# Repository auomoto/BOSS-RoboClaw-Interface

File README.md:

# BOSS-RoboClaw-Interface
 
Interface board that sits on top of the RoboClaw 2x7A controller with a connector for a PI motor.

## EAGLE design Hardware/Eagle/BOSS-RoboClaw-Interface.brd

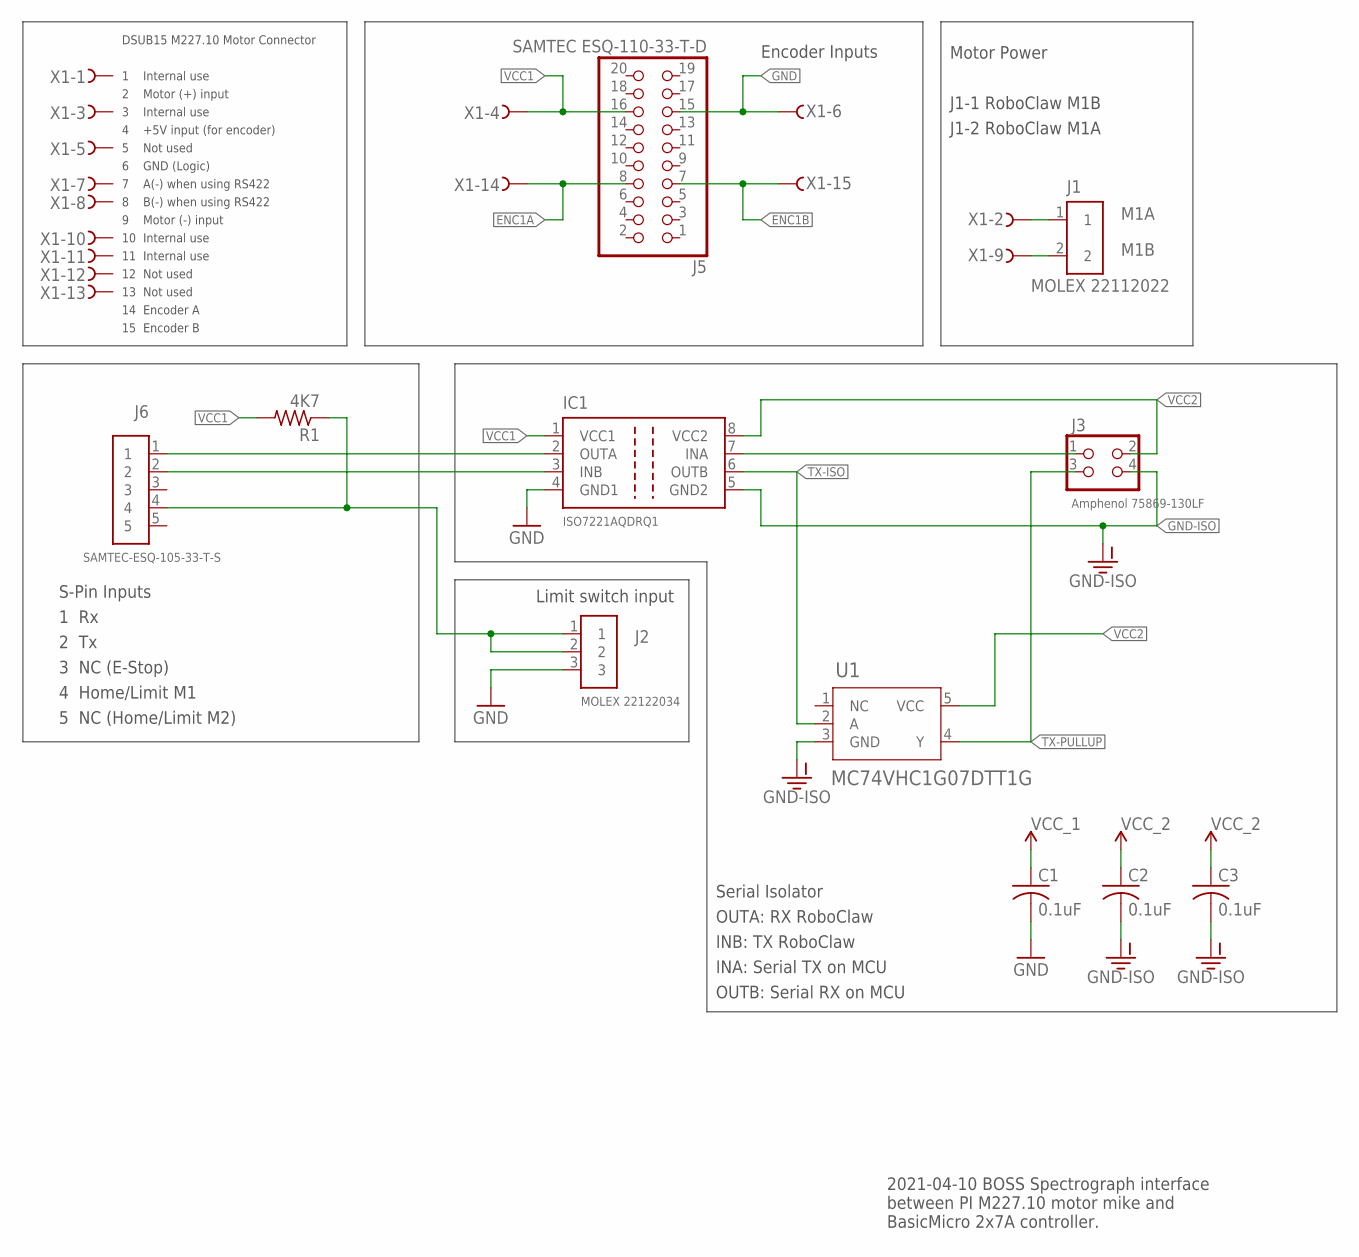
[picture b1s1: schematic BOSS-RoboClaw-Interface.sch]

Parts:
C1, C2, C3: 0.1uF; C0805
IC1: ISO7221AQDRQ1; SO-08-ISO7221
J1: MOLEX 22112022; 1X02-MOLEX-22112022
J2: MOLEX 22122034; 1X03RA-MOLEX-22122034
J3: Amphenol 75869-130LF; 2X02-SHROUD
J5: SAMTEC ESQ-110-33-T-D; 2X10-ESQ-110-33-T-D
J6: SAMTEC-ESQ-105-33-T-S; 1X05-ESQ-105-33-T-S
R1: 4K7; R0805
U1: MC74VHC1G07DTT1G; SOT23-5_ONS-M
X1: Amphenol L77SDAH15SOL2RM8C309; H2R15ST

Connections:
ENC1A: J5.8, X1.14
ENC1B: J5.7, X1.15
GND: C1.2, IC1.4 (GND1), J2.3, J5.15, X1.6
GND-ISO: C2.2, C3.2, IC1.5 (GND2), J3.4, U1.3 (GND)
LIMIT: J2.1, J2.2, J6.4, R1.1
M1A: J1.1, X1.2
M1B: J1.2, X1.9
ROBO-RX: IC1.2 (OUTA), J6.1
ROBO-TX: IC1.3 (INB), J6.2
RX: IC1.7 (INA), J3.1
TX-ISO: IC1.6 (OUTB), U1.2 (A)
TX-PULLUP: J3.3, U1.4 (Y)
VCC1: C1.1, IC1.1 (VCC1), J5.16, R1.2, X1.4
VCC2: C2.1, C3.1, IC1.8 (VCC2), J3.2, U1.5 (VCC)

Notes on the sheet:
DSUB15 M227.10 Motor Connector 1 Internal use 2 Motor (+) input 3 Internal use 4 +5V input (for encoder) 5 Not used 6 GND (Logic) 7 A(-) when using RS422 8 B(-) when using RS422 9 Motor (-) input 10 Internal use 11 Internal use 12 Not used 13 Not used 14 Encoder A 15 Encoder B
Motor Power J1-1 RoboClaw M1B J1-2 RoboClaw M1A
Limit switch input
S-Pin Inputs 1 Rx 2 Tx 3 NC (E-Stop) 4 Home/Limit M1 5 NC (Home/Limit M2)
Serial Isolator OUTA: RX RoboClaw INB: TX RoboClaw INA: Serial TX on MCU OUTB: Serial RX on MCU
Encoder Inputs
2021-04-10 BOSS Spectrograph interface between PI M227.10 motor mike and BasicMicro 2x7A controller.

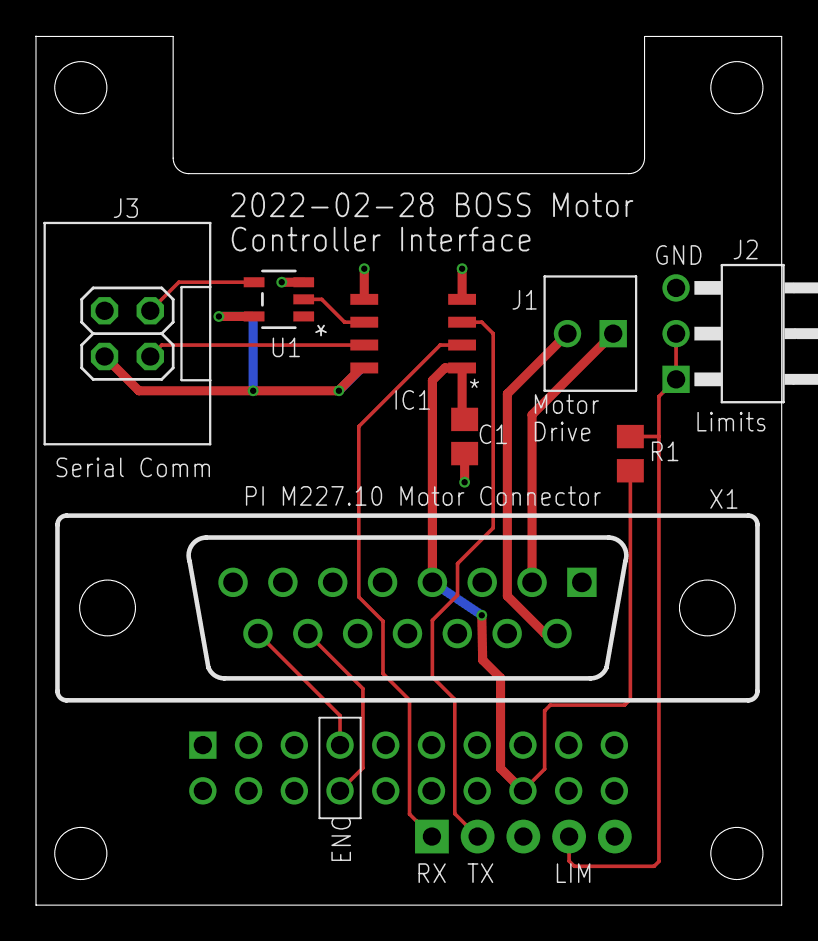
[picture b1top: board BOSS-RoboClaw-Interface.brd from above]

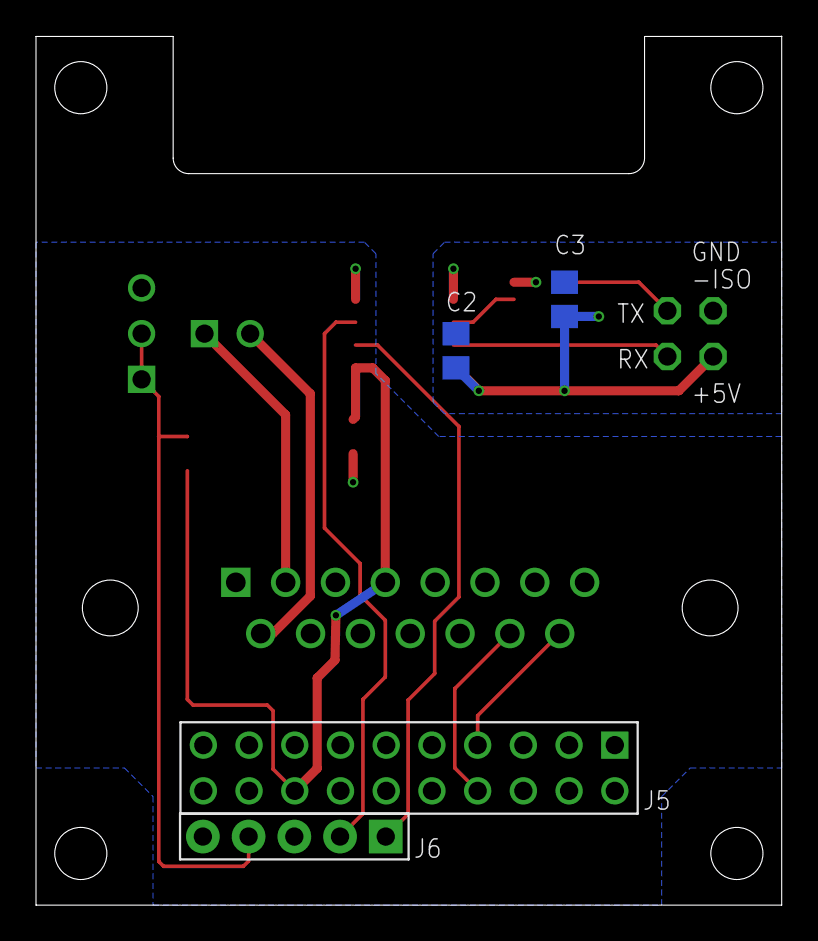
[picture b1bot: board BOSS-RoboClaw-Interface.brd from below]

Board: 2 copper layers, 41.4 x 48.3 mm, 12 parts (4 on the bottom side), 14 nets.

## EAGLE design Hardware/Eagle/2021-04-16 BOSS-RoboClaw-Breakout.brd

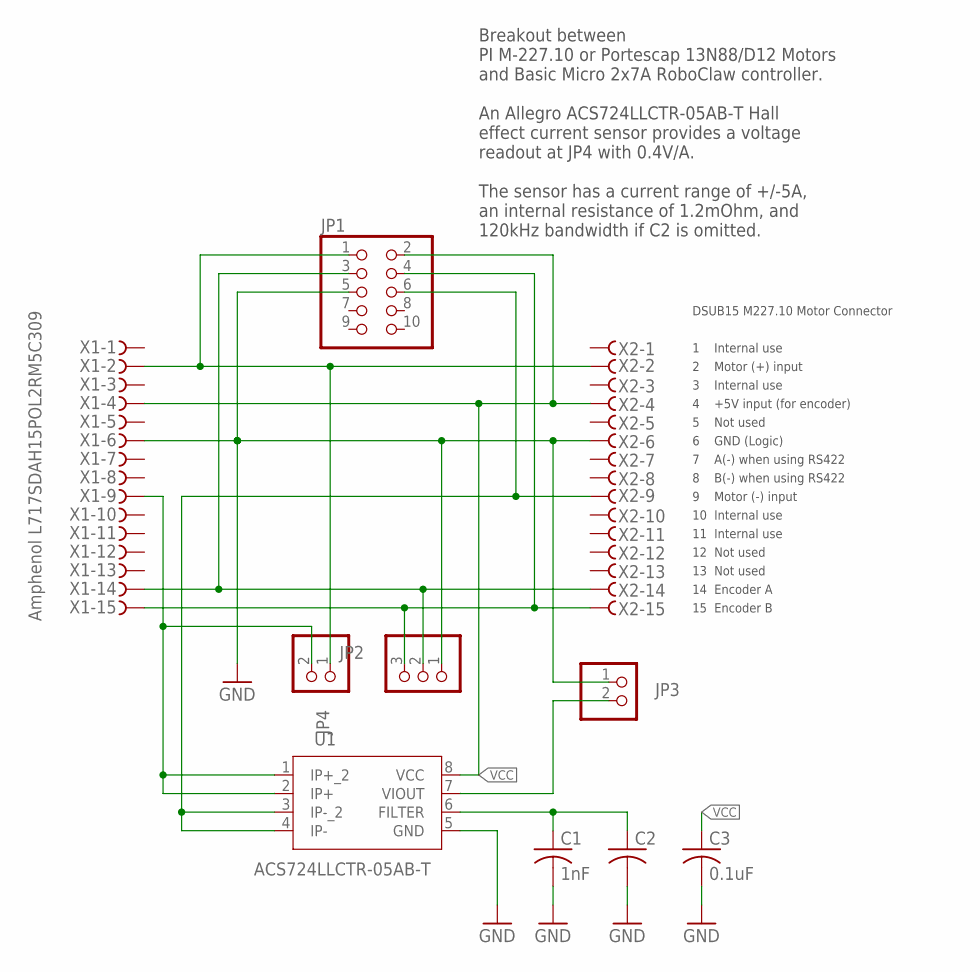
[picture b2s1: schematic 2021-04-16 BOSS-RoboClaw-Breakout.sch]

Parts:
C1: 1nF; C0805
C2: C-USC0805; C0805
C3: 0.1uF; C0805
JP1: PINHD-2X5; 2X05
JP2: PINHD-1X3; 1X03
JP3, JP4: PINHD-1X2; 1X02
U1: ACS724LLCTR-05AB-T; IC8_ACS724LLCTR-05AB-T_ALM
X1: Amphenol L717SDAH15POL2RM5C309; H2M15ST
X2: Amphenol L77SDAH15SOL2RM8C309; H2R15ST

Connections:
ENCA: JP1.3, JP2.2, X1.14, X2.14
ENCB: JP1.4, JP2.3, X1.15, X2.15
FILTER: C1.1, C2.1, U1.6 (FILTER)
GND: C1.2, C2.2, C3.2, JP1.5, JP2.1, JP3.1, U1.5 (GND), X1.6, X2.6
M+: JP1.1, JP4.1, X1.2, X2.2
M-: JP1.6, U1.3 (IP-_2), U1.4 (IP-), X2.9
unnamed: JP4.2, U1.1 (IP+_2), U1.2 (IP+), X1.9
VCC: C3.1, JP1.2, U1.8 (VCC), X1.4, X2.4
VIOUT: JP3.2, U1.7 (VIOUT)

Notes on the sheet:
DSUB15 M227.10 Motor Connector 1 Internal use 2 Motor (+) input 3 Internal use 4 +5V input (for encoder) 5 Not used 6 GND (Logic) 7 A(-) when using RS422 8 B(-) when using RS422 9 Motor (-) input 10 Internal use 11 Internal use 12 Not used 13 Not used 14 Encoder A 15 Encoder B
Breakout between PI M-227.10 or Portescap 13N88/D12 Motors and Basic Micro 2x7A RoboClaw controller. An Allegro ACS724LLCTR-05AB-T Hall effect current sensor provides a voltage readout at JP4 with 0.4V/A. The sensor has a current range of +/-5A, an internal resistance of 1.2mOhm, and 120kHz bandwid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

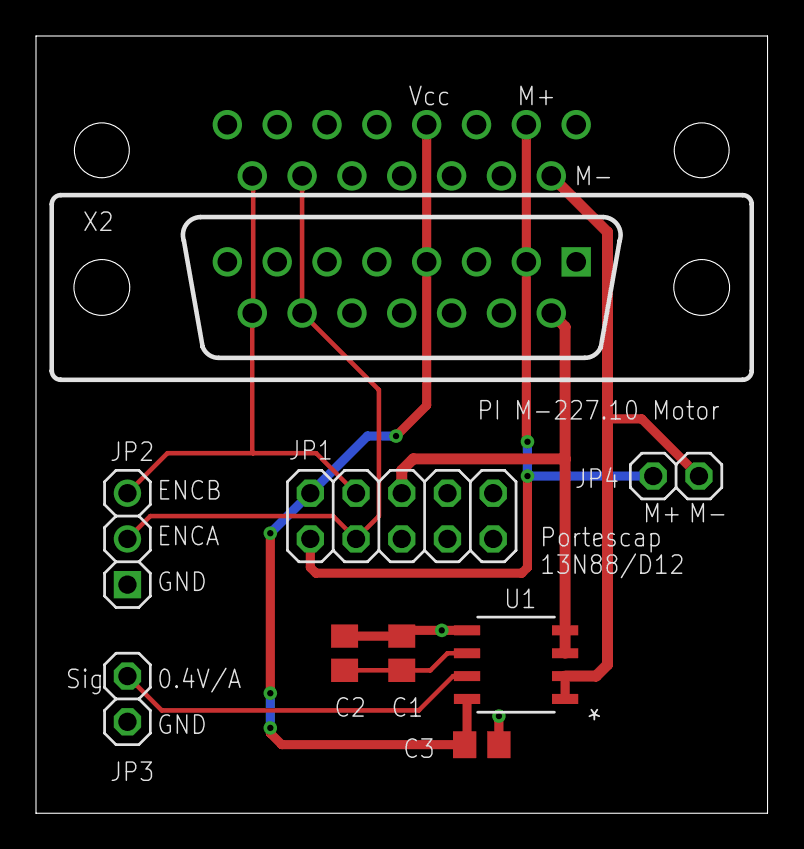
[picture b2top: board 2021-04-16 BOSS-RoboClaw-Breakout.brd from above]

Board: 2 copper layers, 40.6 x 43.2 mm, 10 parts (1 on the bottom side), 9 nets.

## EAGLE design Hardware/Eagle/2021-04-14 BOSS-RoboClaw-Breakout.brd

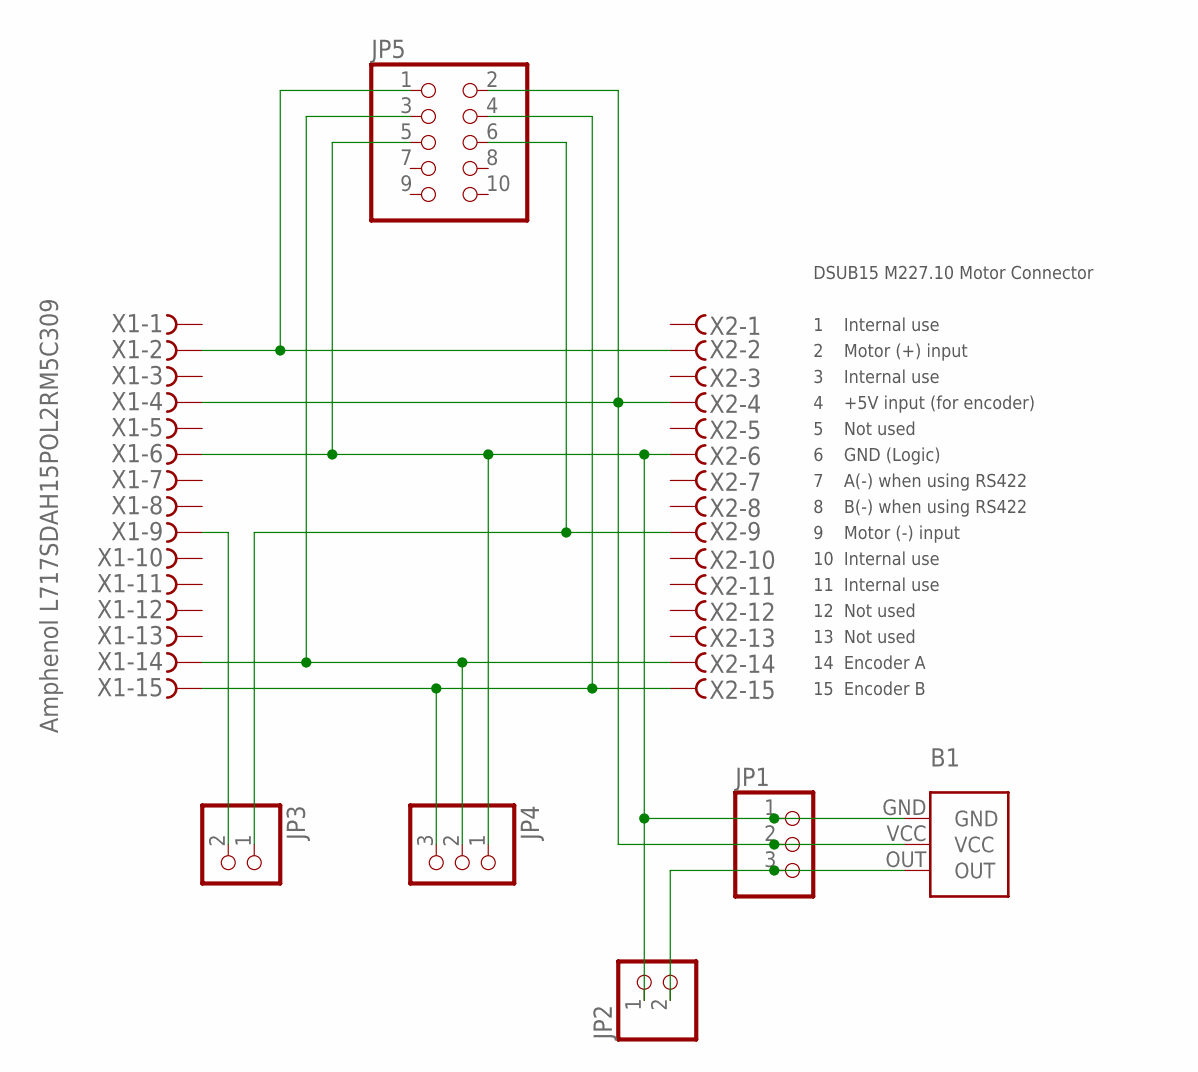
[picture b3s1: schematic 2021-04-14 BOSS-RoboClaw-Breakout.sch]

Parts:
B1: ACS724CARRIER
JP1, JP4: PINHD-1X3; 1X03
JP2, JP3: PINHD-1X2; 1X02
JP5: PINHD-2X5; 2X05
X1: Amphenol L717SDAH15POL2RM5C309; H2M15ST
X2: Amphenol L77SDAH15SOL2RM8C309; H2R15ST

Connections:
ENCA: JP4.2, JP5.3, X1.14, X2.14
ENCB: JP4.3, JP5.4, X1.15, X2.15
GND: B1.GND, JP1.1, JP2.1, JP4.1, JP5.5, X1.6, X2.6
M+: JP5.1, X1.2, X2.2
M-: JP3.1, JP5.6, X2.9
unnamed: JP3.2, X1.9
OUT: B1.OUT, JP1.3, JP2.2
VCC: B1.VCC, JP1.2, JP5.2, X1.4, X2.4

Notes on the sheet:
DSUB15 M227.10 Motor Connector 1 Internal use 2 Motor (+) input 3 Internal use 4 +5V input (for encoder) 5 Not used 6 GND (Logic) 7 A(-) when using RS422 8 B(-) when using RS422 9 Motor (-) input 10 Internal use 11 Internal use 12 Not used 13 Not used 14 Encoder A 15 Encoder B

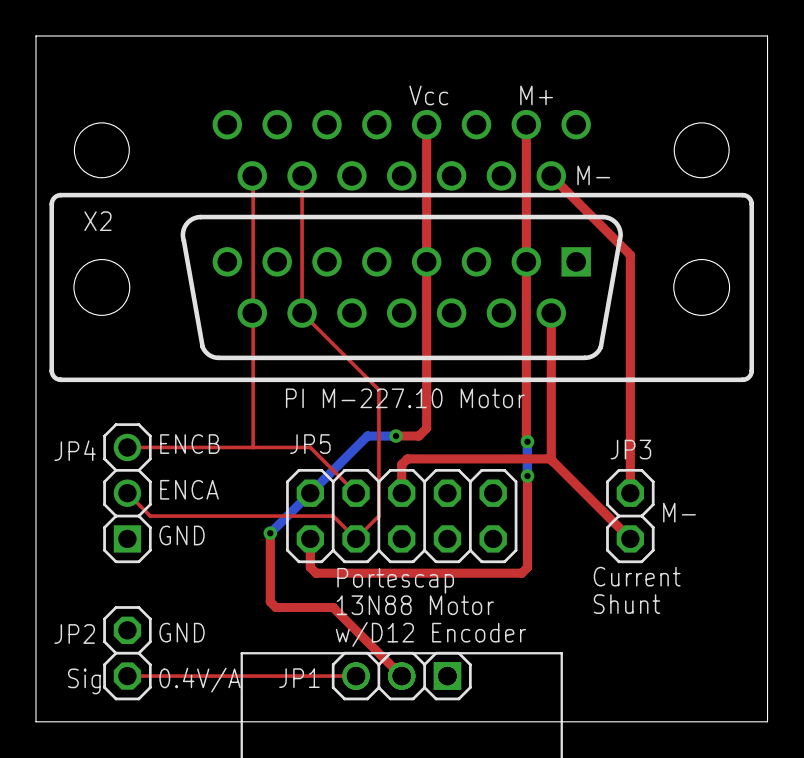
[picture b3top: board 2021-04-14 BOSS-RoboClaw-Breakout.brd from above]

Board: 2 copper layers, 40.6 x 38.1 mm, 8 parts (1 on the bottom side), 8 nets.

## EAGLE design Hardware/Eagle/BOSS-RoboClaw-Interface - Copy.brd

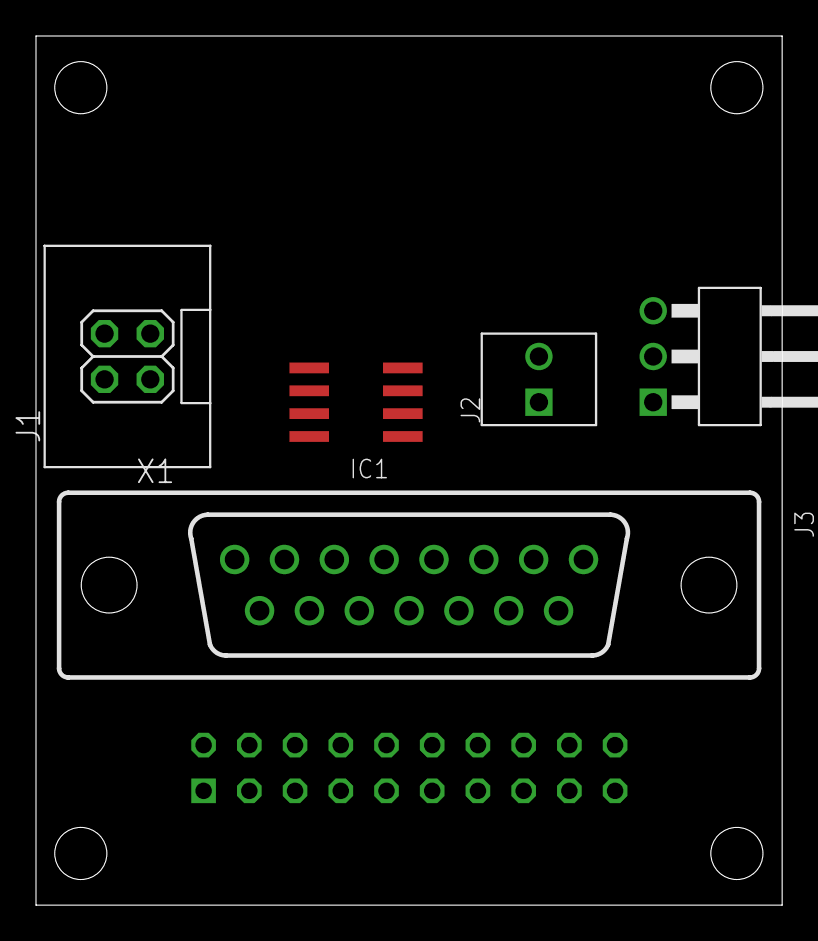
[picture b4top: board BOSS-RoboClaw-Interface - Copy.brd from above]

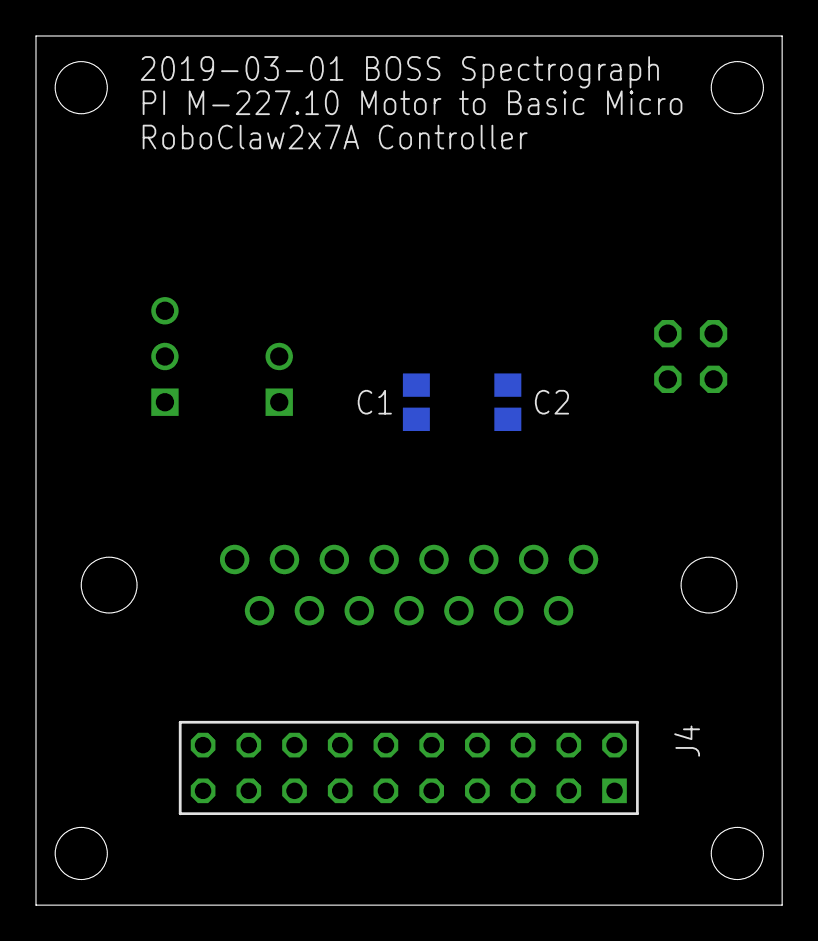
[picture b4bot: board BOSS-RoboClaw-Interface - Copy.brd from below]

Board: 2 copper layers, 41.5 x 48.3 mm, 8 parts (3 on the bottom side), 9 nets, no tracks yet.

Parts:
C1, C2: 0.1uF; C0805
IC1: ISO7221A; SO-08
J1: 2X02-SHROUD
J2: PINHD-1X2-MOLEX-22112022; 1X02-MOLEX-22112022
J3: Molex 22122034; 1X03RA-MOLEX-22122034
J4: FE10-2-SAMTEC-ESW-110-44-S-D
X1: Amphenol L77SDAH15SOL2RM8C309; H2R15ST

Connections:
GND: C1.2, IC1.4, J3.3, X1.6
GND-ISO: C2.2, IC1.5, J1.4
LIMIT/HOME: J3.1, J3.2
M1A: J2.2, X1.9
M1B: J2.1, X1.2
unnamed: IC1.7, J1.1
unnamed: IC1.6, J1.3
VCC1: C1.1, IC1.1, X1.4
VCC2: C2.1, IC1.8, J1.2

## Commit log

2020-11-21 Changed connectors and board outline to be able to use existing screw connectors
2020-11-21 More layout changes
2020-11-23 New headers for RoboClaw interface (need to check connections)
2020-11-23 Swapped ENC-A and ENC-B pins to be consistent
    Also updated the board labels and changed the date to 2020-11-23.
2020-11-23 No changes made; just saved new version
2020-11-23 Removed sheet 2 from the schematic (old notes & BOM)
2020-12-10 Created schematic PDF and saved 2020-11-23 version
2021-01-11 Changed isolator chip to ISO7221AQDRQ1 from ISO7221ADR (better stock)
2021-01-24 Removed Eagle backups for gitignore
2021-02-15 Increased trace width to 0.008 from 0.006 inches
2021-02-20 Added pullup to limit switch line
2021-02-21 Changed limit switch pullup to 4.7K
2021-04-15 Created a motor breakout board
2021-04-16 Added motor power header pins
2021-04-30 Added notes to the breakout board schematic (received the breakout board today)
2021-05-06 Fixed an error in the schematic notes (J4 is motor voltage)
2022-06-14 Includes open drain buffer

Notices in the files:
parts and their libraries:
COPYRIGHT: Copyright (C) 2018 Accelerated Designs. All rights reserved
COPYRIGHT: Copyright (C) 2022 Ultra Librarian. All rights reserved.
